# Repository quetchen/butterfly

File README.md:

# butterfly
Rainbows & Butterflies

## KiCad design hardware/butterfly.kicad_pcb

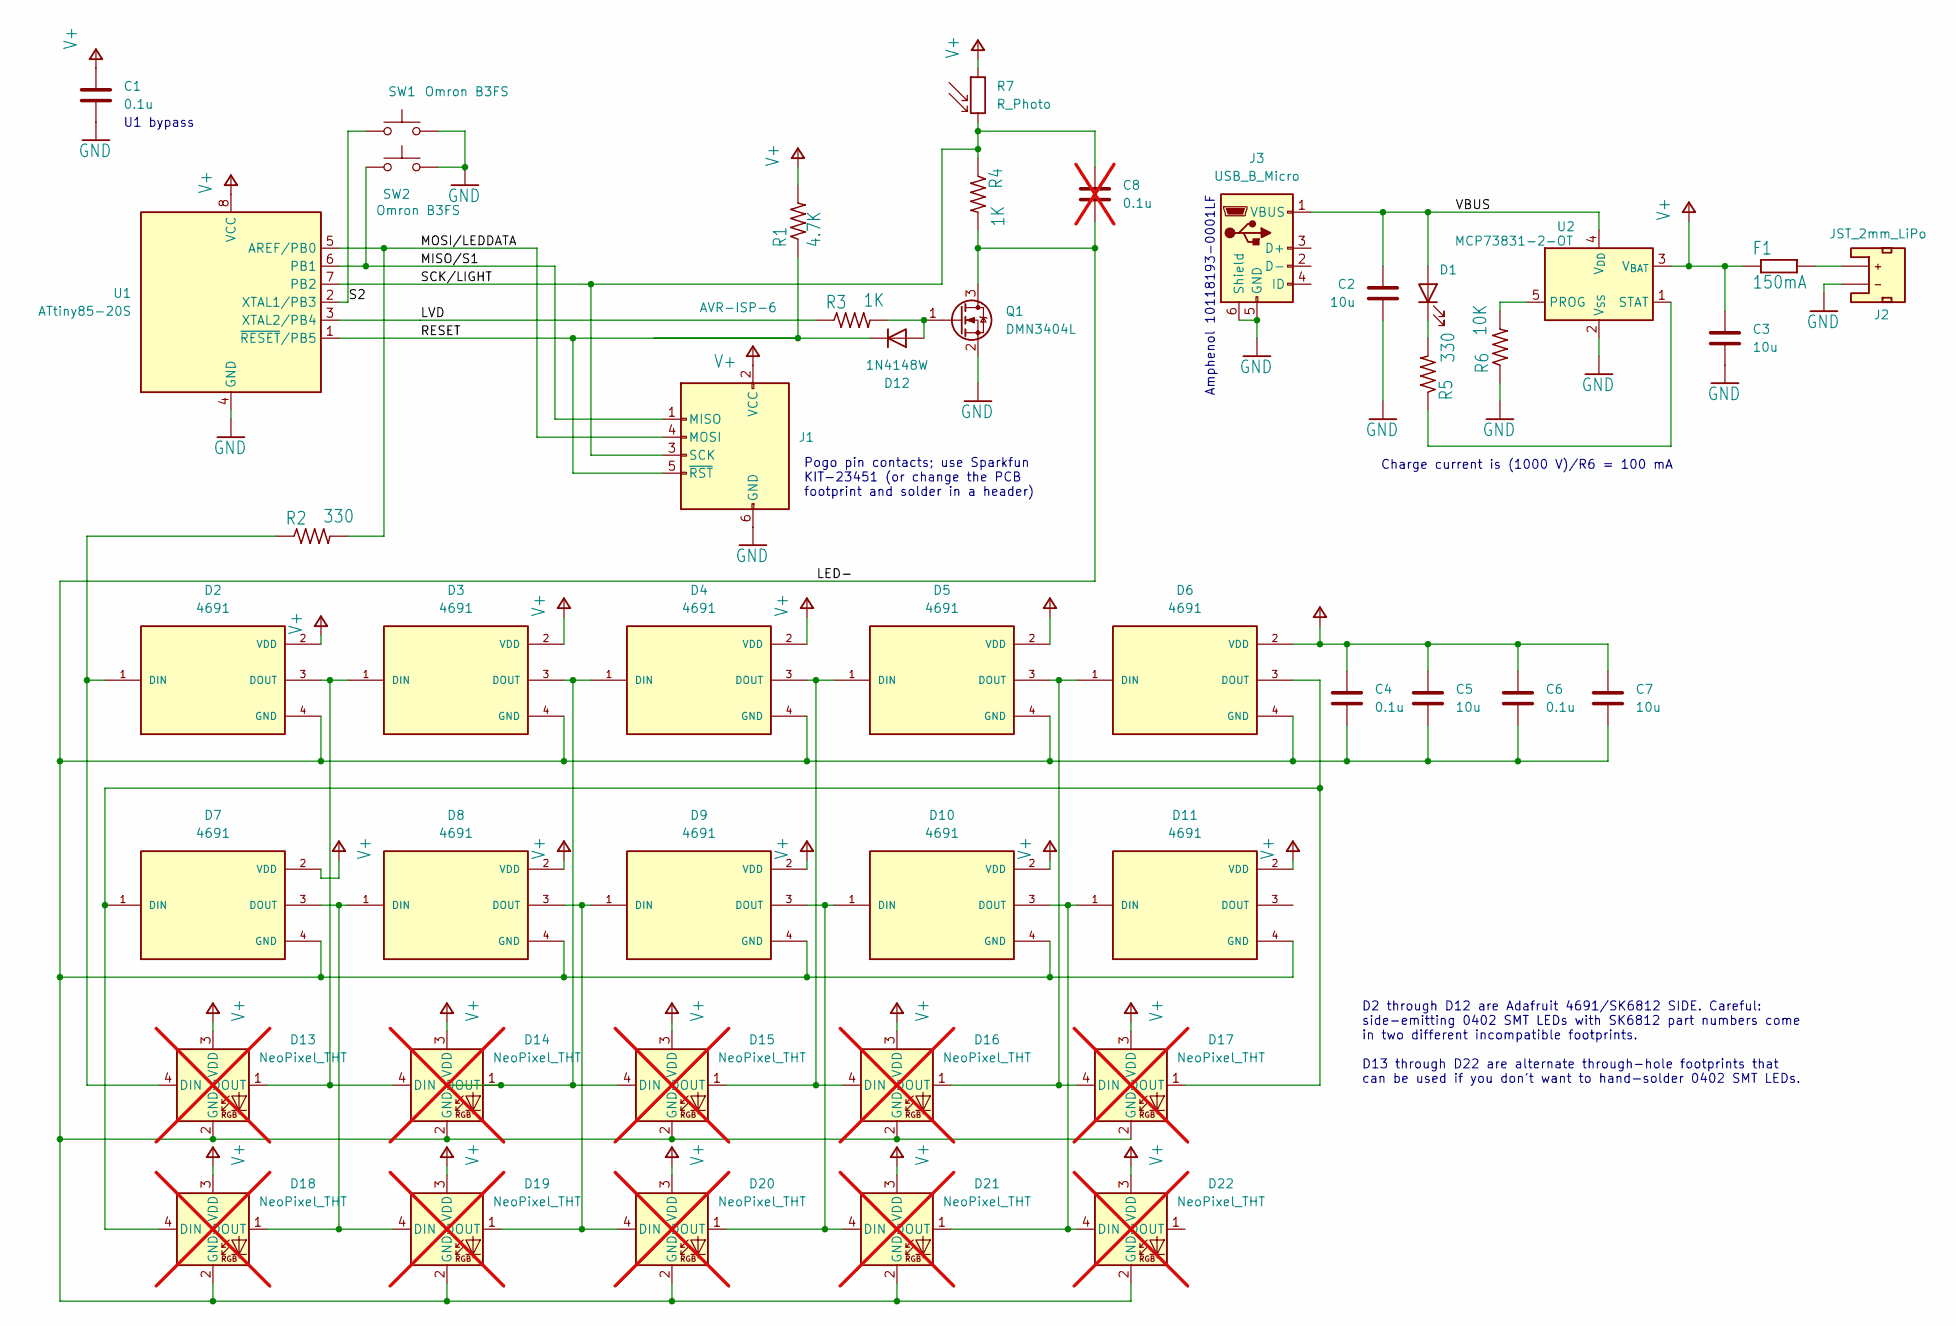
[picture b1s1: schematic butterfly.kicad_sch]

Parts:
C1, C4, C6: 0.1u; C_0603_1608Metric_Pad1.08x0.95mm_HandSolder
C2, C3, C5, C7: 10u; C_0603_1608Metric_Pad1.08x0.95mm_HandSolder
C8: 0.1u; C_0603_1608Metric_Pad1.08x0.95mm_HandSolder; not fitted
D1: LED; LED_0805_2012Metric_Pad1.15x1.40mm_HandSolder
D2, D3, D4, D5, D6, D7, D8, D9, D10, D11: 4691; 4691_handsolder; PARTREV 01
D12: 1N4148W; D_MiniMELF
D13, D14, D15, D16, D17, D18, D19, D20, D21, D22: NeoPixel_THT; LED_D5.0mm-4_RGB; not fitted
F1: 150mA; R_0603_1608Metric_Pad0.98x0.95mm_HandSolder
J1: AVR-ISP-6; PinHeader_2x03_P2.54mm_Vertical
J2: JST_2mm_LiPo; JST_SMD_2.0mm-2
J3: USB_B_Micro; USB_Micro-B_Amphenol_10118193-0001LF_Horizontal
Q1: DMN3404L; SOT-23
R1: 4.7K; R_Axial_DIN0207_L6.3mm_D2.5mm_P7.62mm_Horizontal_nosilk
R2, R5: 330; R_Axial_DIN0207_L6.3mm_D2.5mm_P7.62mm_Horizontal_nosilk
R3, R4: 1K; R_Axial_DIN0207_L6.3mm_D2.5mm_P7.62mm_Horizontal_nosilk
R6: 10K; R_Axial_DIN0207_L6.3mm_D2.5mm_P7.62mm_Horizontal_nosilk
R7: R_Photo; R_LDR_4.9x4.2mm_P2.54mm_Vertical
SW1, SW2: Omron B3FS; SW_SPST_Omron_B3FS-100xP
U1: ATtiny85-20S; SOIC-8_5.3x5.3mm_P1.27mm
U2: MCP73831-2-OT; SOT-23-5

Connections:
/LED-: C4.2, C5.2, C6.2, C7.2, C8.2, D2.4 (GND), D3.4 (GND), D4.4 (GND), D5.4 (GND), D6.4 (GND), D7.4 (GND), D8.4 (GND), D9.4 (GND), D10.4 (GND), D11.4 (GND), D13.2 (GND), D14.2 (GND), D15.2 (GND), D16.2 (GND), D17.2 (GND), D18.2 (GND), D19.2 (GND), D20.2 (GND), D21.2 (GND), D22.2 (GND), Q1.3 (D), R4.2
/LVD: R3.1, U1.3 (XTAL2/PB4)
/MISO/S1: J1.1 (MISO), SW2.1, U1.6 (PB1)
/MOSI/LEDDATA: J1.4 (MOSI), R2.2, U1.5 (AREF/PB0)
/RESET: D12.1 (K), J1.5 (~RST), R1.1, U1.1 (~RESET/PB5)
/S2: SW1.1, U1.2 (XTAL1/PB3)
/SCK/LIGHT: C8.1, J1.3 (SCK), R4.1, R7.2, U1.7 (PB2)
/VBUS: C2.1, D1.2 (A), J3.1 (VBUS), U2.4 (V_{DD})
GND: C1.2, C2.2, C3.2, J1.6 (GND), J2.1 (-), J3.5 (GND), J3.6 (Shield), Q1.2 (S), R6.1, SW1.2, SW2.2, U1.4 (GND), U2.2 (V_{SS})
unnamed: D1.1 (K), R5.2
unnamed: D9.3 (DOUT), D10.1 (DIN), D20.1 (DOUT), D21.4 (DIN)
unnamed: D10.3 (DOUT), D11.1 (DIN), D21.1 (DOUT), D22.4 (DIN)
unnamed: D12.2 (A), Q1.1 (G), R3.2
unnamed: D2.1 (DIN), D13.4 (DIN), R2.1
unnamed: D2.3 (DOUT), D3.1 (DIN), D13.1 (DOUT), D14.4 (DIN)
unnamed: D3.3 (DOUT), D4.1 (DIN), D14.1 (DOUT), D15.4 (DIN)
unnamed: D4.3 (DOUT), D5.1 (DIN), D15.1 (DOUT), D16.4 (DIN)
unnamed: D5.3 (DOUT), D6.1 (DIN), D16.1 (DOUT), D17.4 (DIN)
unnamed: D6.3 (DOUT), D7.1 (DIN), D17.1 (DOUT), D18.4 (DIN)
unnamed: D7.3 (DOUT), D8.1 (DIN), D18.1 (DOUT), D19.4 (DIN)
unnamed: D8.3 (DOUT), D9.1 (DIN), D19.1 (DOUT), D20.4 (DIN)
unnamed: F1.2, J2.2 (+)
unnamed: R6.2, U2.5 (PROG)
unnamed: R5.1, U2.1 (STAT)
V+: C1.1, C3.1, C4.1, C5.1, C6.1, C7.1, D2.2 (VDD), D3.2 (VDD), D4.2 (VDD), D5.2 (VDD), D6.2 (VDD), D7.2 (VDD), D8.2 (VDD), D9.2 (VDD), D10.2 (VDD), D11.2 (VDD), D13.3 (VDD), D14.3 (VDD), D15.3 (VDD), D16.3 (VDD), D17.3 (VDD), D18.3 (VDD), D19.3 (VDD), D20.3 (VDD), D21.3 (VDD), D22.3 (VDD), F1.1, J1.2 (VCC), R1.2, R7.1, U1.8 (VCC), U2.3 (V_{BAT})

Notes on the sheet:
Amphenol 10118193-0001LF
Pogo pin contacts; use Sparkfun KIT-23451 (or change the PCB footprint and solder in a header)
Charge current is (1000 V)/R6 = 100 mA
D2 through D12 are Adafruit 4691/SK6812 SIDE. Careful: side-emitting 0402 SMT LEDs with SK6812 part numbers come in two different incompatible footprints. D13 through D22 are alternate through-hole footprints that can be used if you don't want to hand-solder 0402 SMT LEDs.
U1 bypass

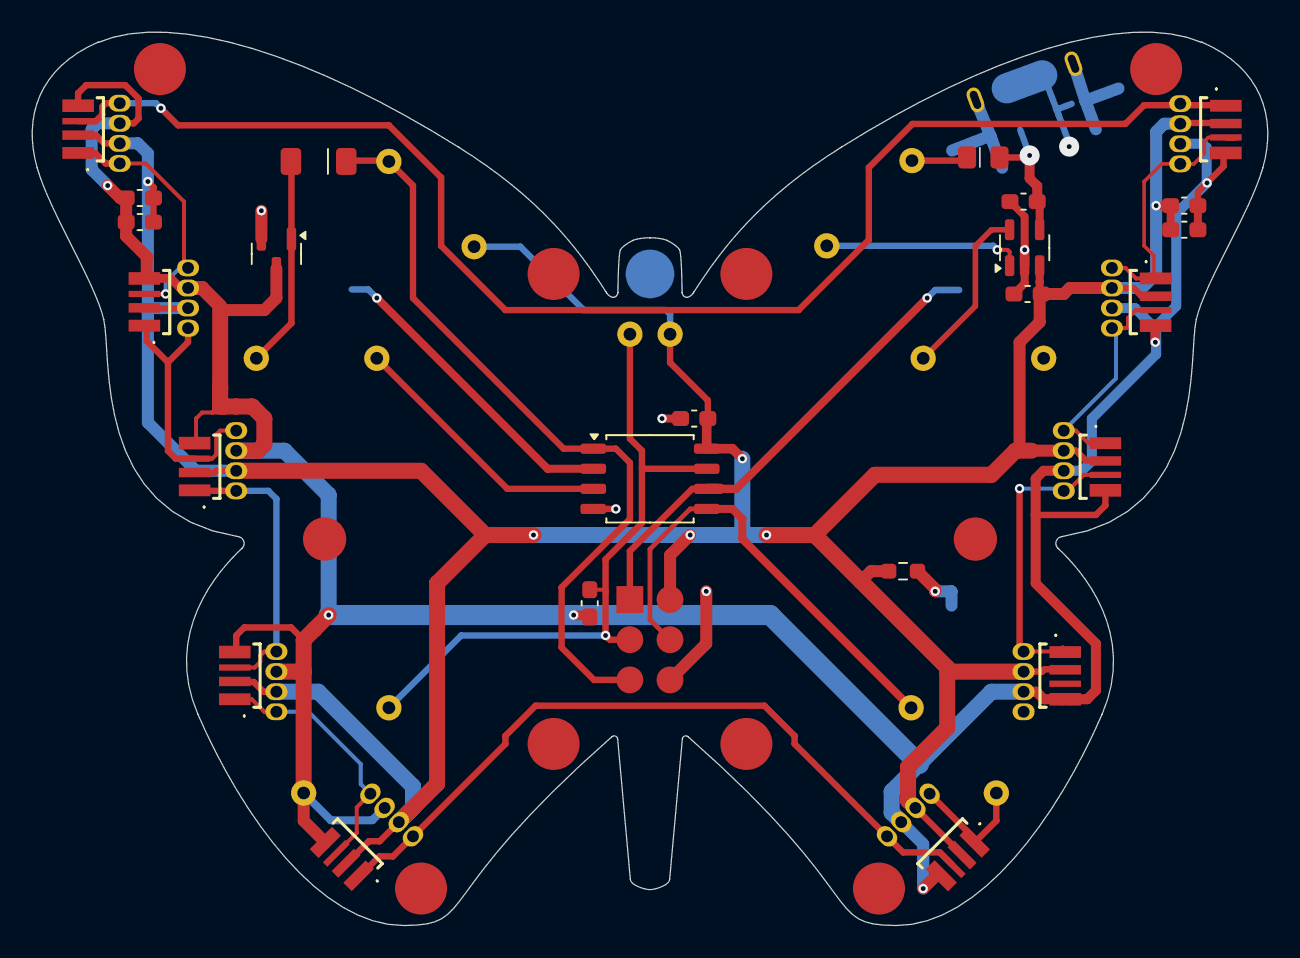
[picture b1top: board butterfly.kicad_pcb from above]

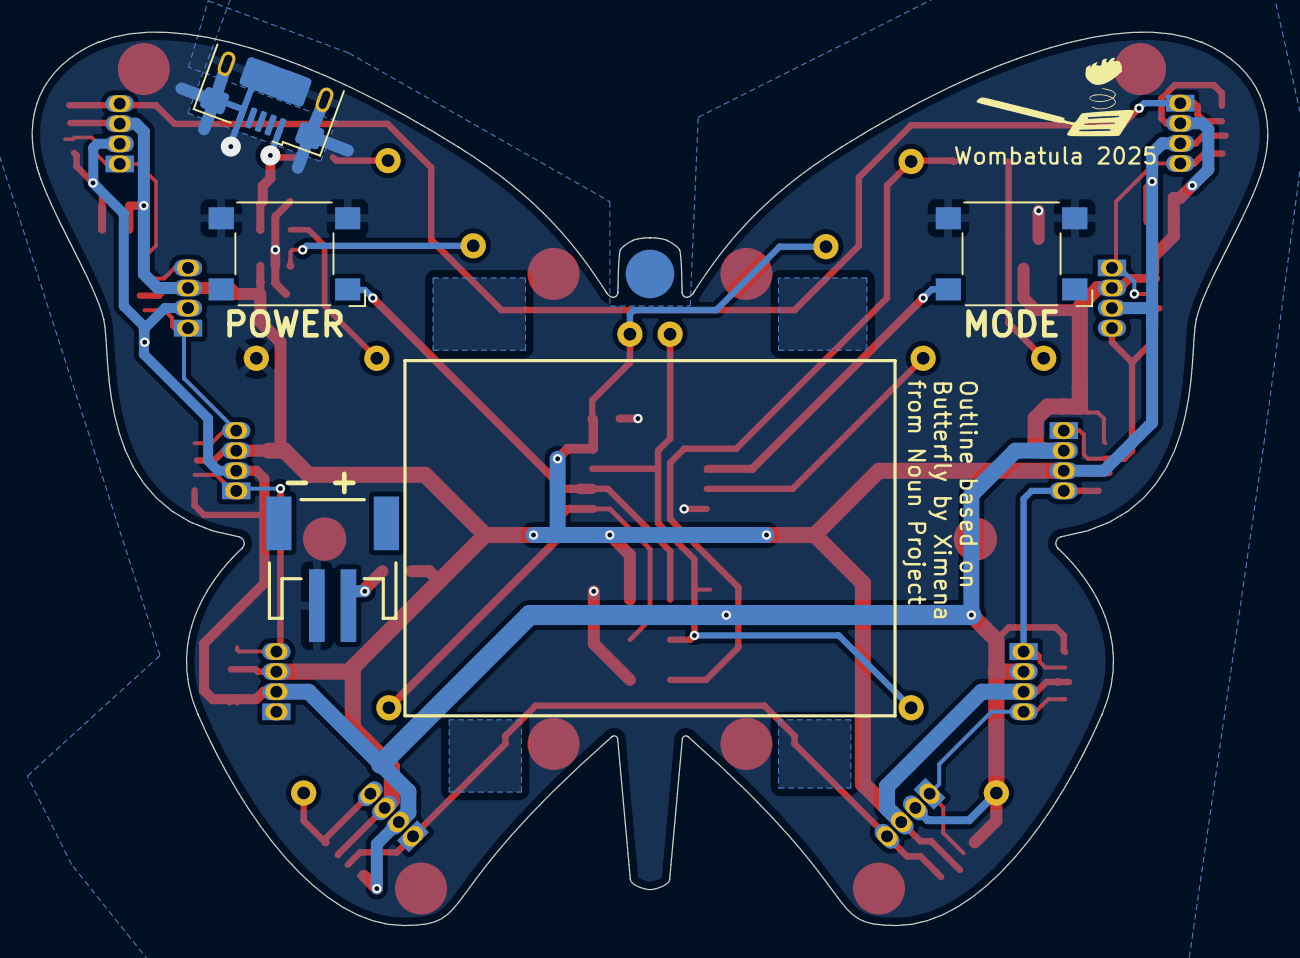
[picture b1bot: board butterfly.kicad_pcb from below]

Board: 2 copper layers, 78.1 x 56.5 mm, 46 parts (4 on the bottom side), 25 nets.

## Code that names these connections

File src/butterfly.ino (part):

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#include <avr/sleep.h>
#include <avr/wdt.h>

#define PIN_LED PIN_PB0
#define PIN_LIGHT PIN_PB2
#define PIN_LVD PIN_PB4
#define LED_COUNT 10
#define BRIGHT_INIT 32

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};

#define BUTTON_DEBOUNCE_MS 100
const PROGMEM uint8_t button_pin[] = {PIN_PB1, PIN_PB3};
volatile uint8_t button_count[] = {0, 0};
volatile bool button_pressed[] = {false, false};
volatile bool button_read[] = {false, false};
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  ACSR   |= (1 << ACD);


  pinMode(PIN_LVD, OUTPUT);
  pinMode(PIN_LED, OUTPUT);
  pinMode(PIN_LIGHT, INPUT);
  pinMode(PIN_PB1, INPUT_PULLUP);
  pinMode(PIN_PB3, INPUT_PULLUP);
  digitalWrite(PIN_LVD, HIGH);

  FastLED.setBrightness(BRIGHT_INIT);
  FastLED.addLeds<WS2812B, PIN_LED, GRB>(leds, LED_COUNT);
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    // enable WDT interrupt, prescaler = 1001 (8 sec)
//  WDTCR = 0b11111001;

    // enable pin change interrupt on PB1
    PCMSK |= (1 << PCINT1);
    GIMSK |= (1 << PCIE);
}
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      FastLED.clear(true);
      // if we don't do this the LEDs will still be able to sink current through the data input
      pinMode(PIN_LED, INPUT);
      digitalWrite(PIN_LVD, LOW);
    }  else if (uvlo && voltage < UVLO_RELEASE){
      uvlo = false;
      digitalWrite(PIN_LVD, HIGH);
      pinMode(PIN_LED, OUTPUT);
      // re-enable ADC
      ADCSRA |= (1 << ADEN);
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  if (get_button(0)){
    FastLED.clear(true);
    pinMode(PIN_LED, INPUT);
    digitalWrite(PIN_LVD, LOW);
    set_sleep_mode(SLEEP_MODE_PWR_DOWN);

    // disable button debounce
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      sleep_disable();

      delay(1);
      if (digitalRead(PIN_PB1) == HIGH) {
        // button released; back to bed
        wake_count = 0;
        sleep_enable();
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    // enable the ADC
    ADCSRA |= (1 << ADEN);
    
    digitalWrite(PIN_LVD, HIGH);
    pinMode(PIN_LED, OUTPUT);
    //re-enable button debounce
    TIMSK |= (1 << OCIE0A);
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
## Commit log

2025-06-01 Add kicad board files
2025-06-01 add firmware code
